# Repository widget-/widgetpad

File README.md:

# Widgetpad v0

Hi, I'm Widget, and these are the files for my ITG dance/travel pad.

This is the "v0" version, currently in prototype status. I don't plan
on deviating too far from these plans, but there are more adjustments
I still want to make to make the pad easier to manufacture, easier to
fork the source code for, and have it perform more consistently.

You can find me on the Stamina Nation discord causing problems in #pads.

If you live in Chicago and can pass stamina 16's or higher, I would be
interested in having you try out the prototype in person for feedback.
Let me know on Discord.

## Motivation

Current pads either suck or are >$1000. LTEKs are acceptable but need
significant modding using custom microcontrollers and the fragile "penny
mod", so why not just make a new pad?

Currently it's mainly competing with Bandit's
[Build This Travel Pad](https://www.youtube.com/watch?v=y6wGYLE0YI4)
and [Bandit's Terrific Travel Pad](https://github.com/BanditsTerrificTravelPad/bttp)
budget designs.

## Specs

* Aluminum extrusion frame (2020 profile)
* 1/2" acrylic panels
* Arduino Pro Micro microcontroller (but with plans to switch to Teensy
  4.0)
* Force-sensitive resistors for configurable sensitivity
  * Allows for rather extreme sensitivity if made with good tolerances
* Optional LED grid PCBs (WS2812C LEDs)

## License

GNU GPL v2. See LICENSE for full text.

## Demo

## Requirements

### Materials

* Arduino Pro Micro or Teensy 2.0 or higher
* 4x 220 ohm resistors
* Some wire to extend FSR connections
* Panels, cut or precut:
  * Either
    * 4x 12mm thickness 280mm x 280mm acrylic panels (1/2" thickness
      11"x11") or larger
  * Or
    * 1x 280mm x 280mm precut acrylic center panel
    * 4x 280mm x 125mm precut acrylic side panels
    * 4x 125mm x 125mm precut acrylic corner panels (optional)
  * Optionally, acetal (a.k.a. POM, Delrin) as a slipperier center panel
    instead of acrylic
* Aluminum extrusion (2020 profile)
  * All taps should be M6 taps with 10mm depth
    * Extra depth is acceptable but may require longer M6 threaded rods
  * 2x 544mm extrusions
    * Drill 6mm at holes at 10mm, 129.5mm, 414.5mm, and 534mm
    * Countersink these holes for your 6mm bolts as well
  * 4x 504mm extrusions, both ends tapped
    * Drill 6mm holes at 109.5mm and 394.5mm
    * For 2 extrusions, countersink these holes for your 6mm bolts as
      well
    * For the other 2 extrusions, extra holes for wiring recommended
  * 2x 265mm extrusions, both ends tapped
    * Extra holes through the center for wiring recommended
  * 4x 99.5mm extrusions, both ends tapped
    * Extra holes through the center for wiring recommended
* Force sensitive resistors (4x 200mm [Interlink 408](https://buyinterlinkelectronics.com/collections/new-standard-force-sensors/products/fsr-model-408-200mm-length) or 8x
  [Interlink 400](https://buyinterlinkelectronics.com/collections/new-standard-force-sensors/products/fsr-model-400))
* 12x countersunk M6x30mm bolts
* 12x hex-head M6x30mm bolts
* 4x M6x40mm threaded rods
* 16x M6 threaded inserts for plastic
* 40x M5x10 bolts
* 40x M5 hammer nuts for 2020 aluminum extrusion
* An "engineering" filament for 3D printed parts, such as PETG, nylon,
  or polycarbonate
* Optional: cross brackets and angle brackets for stability
* Optional: rubber bumpers for floor safety and/or better pad sensitivity
* Optional: 128 [WS2812C-5050](https://lcsc.com/product-detail/Light-Emitting-Diodes-LED_5050-RGBIntegrated-Light-4Pin_C114587.html) LEDs for PCBs
* Optional: 8x 1x2 2.54mm-pitch right-angle male PCB headers for PCBs
* Optional: 4x [5.04mm-pitch 1x2 screw terminals](https://lcsc.com/product-detail/Screw-terminal_Ningbo-Kangnex-Elec-WJ500V-5-08-2P_C8465.html) for PCBs
* Optional: 8x [5.04mm-pitch 1x3 screw terminals](https://lcsc.com/product-detail/Screw-terminal_Ningbo-Kangnex-Elec-WJ500V-5-08-3P_C72334.html) for PCBs

### Equipment

* Table saw if acrylic cutting needed
* Drill press with 6mm (1/4") drill bit and 45° countersink bit
* Table router and roundover bit or lots of sandpaper for smooth edges
* 3mm and 4mm allen keys
* 3D printer for panel mounts
* A heated tool of some sort, such as a soldering iron or a lighter and
  a rod of some type, for inserting the threaded inserts
* Soldering iron is required if assembling PCBs
* DuPont wire crimpers may be useful for making "extension cords" for
  the FSR connectors

### 3D printed parts

3D printed parts can be found in the `3d/` folder.

Parts are designed using [OpenSCAD](https://openscad.org/) with the
[BOSL2](https://github.com/revarbat/BOSL2) library. OpenSCAD nightlies
and BOSL2 master branch are recommended.

Corner bracket mounts will need to be 3D printed to connect the panels
to the aluminum frame.

Strong filaments, at a minimum PETG but preferably
nylon or polycarbonate will be required. Brittle filaments like PLA,
ABS, HIPS, and ASA may crack. High-rigidity TPU filaments (Shore
hardness 98A or higher) may work, but soft filaments may cause the
panels to slide during play.

A soldering iron or other heating tool will be needed to melt the
threaded inserts into the 3D printed part for the panels to connect to.

PCB mounts may also be 3D printed.

A housing will eventually be designed for the microcontroller but not
as part of v0.

### PCBs

#### Microcontroller breakout

The microcontroller breakout is for a Teensy 4.0 or Teensy 4.1.

The Teensy 4.0 will allow control of up to 10 FSRs, which can map to
up to 10 panels, or 2 FSRs on up to 5 panels.

The Teensy 4.1 will allow control of up to 18 FSRs, which allows an
amount of flexibility with regards to a high-end setup:

* 4 FSRs on each of 4 panels (dance)
* 2 FSRs on each of 8 or 9 panels (techno)
* 2 or 3 FSRs on 4 panels and 4 on a center panel (pump)
* 4 FSRs on 4 panels, and 2 on a center panel (pump)

The breakout also has:

* A 3-pin JST-HX connection for panel LEDs
* 9 LEDs for checking FSR pressed status
* 4 external buttons, for an external arcade button assembly
* 3 internal buttons for controlling LED brightness, and triggering
  an as-yet-unwritten pad calibration
* A buzzer or speaker, to add audio "tactility" to pressing the panels
* A jumper to bridge USB power with the external power input for LEDs

The breakout is designed using KiCAD and uses
[teensy_library](https://github.com/XenGi/teensy_library) and
[teensy.pretty](https://github.com/XenGi/teensy.pretty) by
[XenGi](https://github.com/XenGi), released under the BSD license.

#### Panels

The PCBs are designed using [KiCAD](https://www.kicad.org/).

The PCBs each hold an 8x4 grid of WS2812C LEDs. An external 5V power
source is recommended if using LEDs.

Each PCB has screw terminals for connecting the WS2812C inputs and
outputs. In addition, there are 3 positions of screw terminals and
headers for connecting one or more FSRs. Multiple FSRs would be wired
in parallel.

## Construction

### Frame

1) Cut all aluminum extrusion pieces to length, if not precut
2) Cut drills and countersinks in extrusion
3) Tap all extrusion pieces 10mm deep except the two longest ones, if
   not pretapped
4) Use threaded rods to attach small extrusions "through" the two longer
   center ones
5) Bolt the four second-longest extrusions to the longest two extrusions
6) Insert threaded inserts (using heat) into 3D printed panel mounts
7) Attach 3D printed panel mounts to corners of frame using M5 hammer
   nuts
8) Optionally add cross braces and corner brackets, and add rubber feet
   to the bottom of the frame

### Panels

1) Cut all panels to correct size
2) Preferably using a drill press, cut holes 30mm inset from each corner
   * Four holes on the center panel
   * Two adjacent holes on the edge panels
   * Two opposing holes on the corner panels
3) Use a countersink bit to countersink the holes
4) Using a table router with a roundover bit or lots of sandpaper,
   smooth the edges so that your socks don't get torn up

### Wiring

This pad uses typical wiring for FSR-based pads. Each FSR should connect
to an analog pin an the microcontroller with a 220 ohm pulldown resistor
with the other side connected to VCC.

LED boards will need a connection to VCC, GND, and a data pin, typically
D10 on the Arduino Pro Micro.

An external 5V power source is recommended if using LEDs.

One or more large capacitors (47μF or larger) across +5V and GND may
help with signal stability if the LEDs are causing noise in the FSR
signals.

See also [this diagram](https://cdn.discordapp.com/attachments/591851159795400734/841802090543054849/Untitled-1.png) by Bandit.

## Dimensions

The dimensions are currently calculated using Fusion 360, but I hate
Fusion 360 so eventually I'll change it over to OpenSCAD as well.

## Firmware

The firmware is still a work in progress and can be found at
[widget-/bttp-firmware](https://github.com/widget-/bttp-firmware). It is
a fork of Bandit's [BTTP](https://github.com/BanditsTerrificTravelPad/bttp)
pad's firmware.

Currently it supports joystick or keyboard input, and allows an arbitrary
amount of buttons with corresponding optional LED strips. Sensitivity
can be adjusted either in the firmware or with a tool such as the
[bttp-config-tool](https://github.com/BanditsTerrificTravelPad/bttp-config-tool).

## Special thanks

* Bandit, for motivating me to make this pad, as well as giving me one
  of his prototype pads to play on.
* [dominick](https://www.youtube.com/channel/UCpeNRVOVrqx_lras7hbOOrQ)
  and [teejusb](https://github.com/teejusb) for their help and experience
* The rest of #pads for keeping me motivated
* [South Side Hackerspace](https://sshchicago.org/), for having all the equipment used to create
  the prototype

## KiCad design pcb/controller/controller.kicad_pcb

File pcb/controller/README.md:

# Teensy 4.0/4.1 Breakout PCB

This is a breakout board for the Teensy 4.0 or Teensy 4.1
microcontroller, intended for use with custom dance pads for games like
ITG and Pump It Up.

This PCB is designed in KiCAD. If the dependencies for the board are not
detected automatically, add the common_lib folder next to this folder
to your KiCAD's search paths for both libraries and footprints.

## Features

* Many FSR outputs with 10kΩ resistors
  * 18 outputs with Teensy 4.1
  * 10 outputs with Teensy 4.0
* Status LEDs for FSR activation status
* 3-pin JST-XH connector for WS2811/WS2812 panel LED boards or strips
* Internal buttons for controlling LED brightness and activating pad
  automatic calibration
* Connection points for external navigation buttons
* Buzzer for audio feedback
* DC barrel jack connector for external LED power
  * Jumper for using USB power to power LEDs instead
* Headers for all soldered Teensy pins, to allow for use cases beyond
  just this board

## License

GNU GPL v2. See the LICENSE file in this project's root for full text.

## Schematic

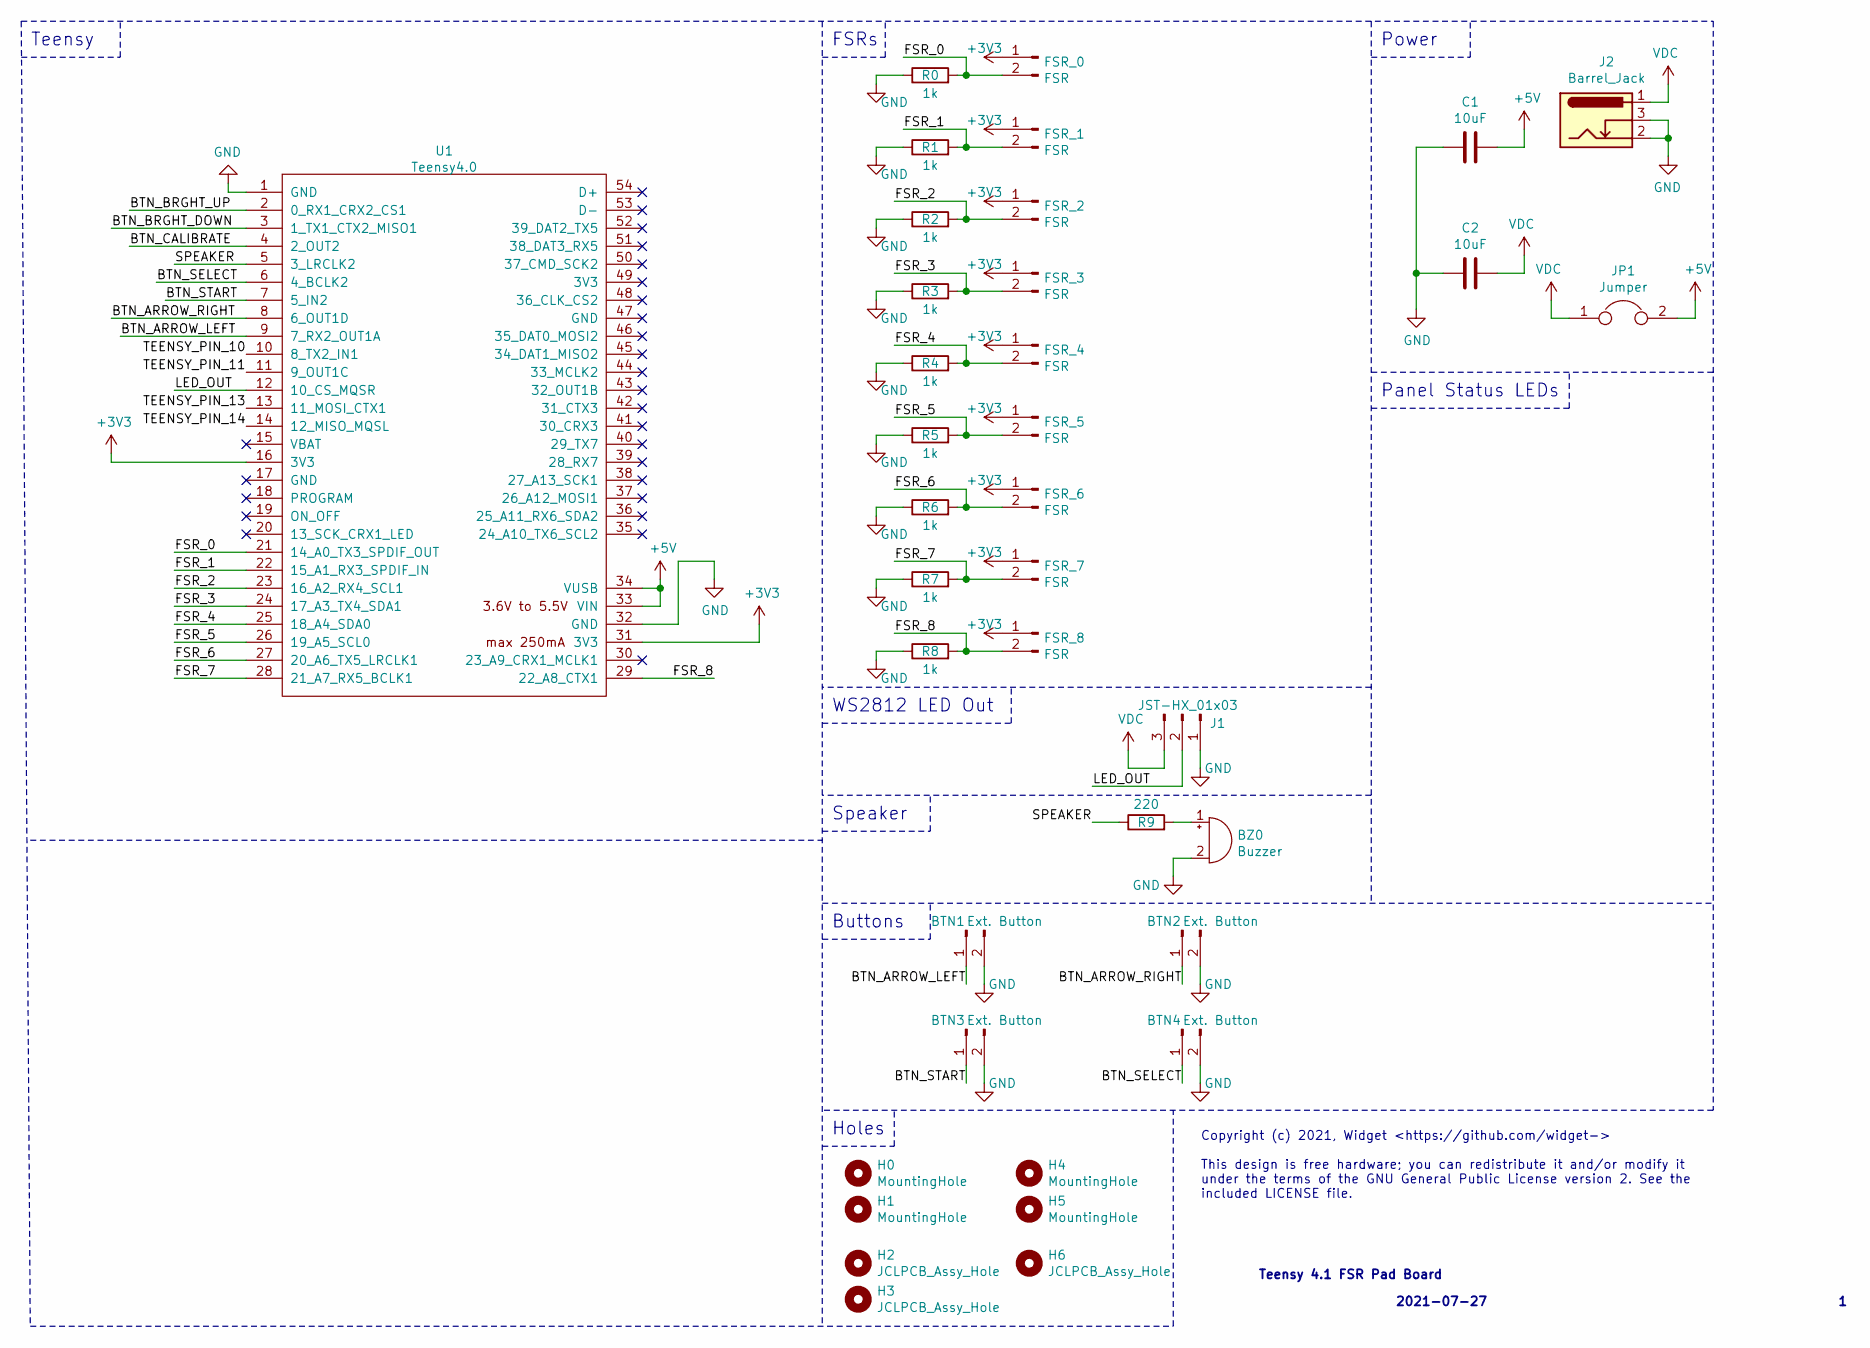
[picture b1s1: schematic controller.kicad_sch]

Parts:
BTN1, BTN2, BTN3, BTN4: Ext. Button; PinHeader_1x02_P2.54mm_Horizontal
BZ0: Buzzer; Buzzer_12x9.5RM7.6
C1, C2: 10uF; C_0805_2012Metric
FSR_0, FSR_1, FSR_2, FSR_3, FSR_4, FSR_5, FSR_6, FSR_7, FSR_8: FSR; PinHeader_1x02_P2.54mm_Horizontal
H0, H1, H4, H5: MountingHole; MountingHole_3.2mm_M3
H2, H3, H6: JCLPCB_Assy_Hole; JCLPCB_Assembly_Hole
J1: JST-HX_01x03; JST_XH_B3B-XH-AM_1x03_P2.50mm_Vertical
J2: Barrel_Jack; XKB_Connectivity_DC-044A-2.5A
JP1: Jumper; PinHeader_1x02_P2.54mm_Vertical
R0, R1, R2, R3, R4, R5, R6, R7, R8: 1k; R_0805_2012Metric_Pad1.20x1.40mm_HandSolder
R9: 220; R_0805_2012Metric_Pad1.20x1.40mm_HandSolder
U1: Teensy4.0; teensy40

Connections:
+3V3: FSR_0.1, FSR_1.1, FSR_2.1, FSR_3.1, FSR_4.1, FSR_5.1, FSR_6.1, FSR_7.1, FSR_8.1, U1.16 (3V3), U1.31 (3V3)
+5V: C1.1, JP1.2, U1.33 (VIN), U1.34 (VUSB)
/BTN_ARROW_LEFT: BTN1.1, U1.9 (7_RX2_OUT1A)
/BTN_ARROW_RIGHT: BTN2.1, U1.8 (6_OUT1D)
/BTN_BRGHT_DOWN: U1.3 (1_TX1_CTX2_MISO1)
/BTN_BRGHT_UP: U1.2 (0_RX1_CRX2_CS1)
/BTN_CALIBRATE: U1.4 (2_OUT2)
/BTN_SELECT: BTN4.1, U1.6 (4_BCLK2)
/BTN_START: BTN3.1, U1.7 (5_IN2)
/FSR_0: FSR_0.2, R0.2, U1.21 (14_A0_TX3_SPDIF_OUT)
/FSR_1: FSR_1.2, R1.2, U1.22 (15_A1_RX3_SPDIF_IN)
/FSR_2: FSR_2.2, R2.2, U1.23 (16_A2_RX4_SCL1)
/FSR_3: FSR_3.2, R3.2, U1.24 (17_A3_TX4_SDA1)
/FSR_4: FSR_4.2, R4.2, U1.25 (18_A4_SDA0)
/FSR_5: FSR_5.2, R5.2, U1.26 (19_A5_SCL0)
/FSR_6: FSR_6.2, R6.2, U1.27 (20_A6_TX5_LRCLK1)
/FSR_7: FSR_7.2, R7.2, U1.28 (21_A7_RX5_BCLK1)
/FSR_8: FSR_8.2, R8.2, U1.29 (22_A8_CTX1)
/LED_OUT: J1.2, U1.12 (10_CS_MQSR)
/SPEAKER: R9.1, U1.5 (3_LRCLK2)
/TEENSY_PIN_10: U1.10 (8_TX2_IN1)
/TEENSY_PIN_11: U1.11 (9_OUT1C)
/TEENSY_PIN_13: U1.13 (11_MOSI_CTX1)
/TEENSY_PIN_14: U1.14 (12_MISO_MQSL)
GND: BTN1.2, BTN2.2, BTN3.2, BTN4.2, BZ0.2 (+), C1.2, C2.2, J1.1, J2.2, J2.3, R0.1, R1.1, R2.1, R3.1, R4.1, R5.1, R6.1, R7.1, R8.1, U1.1 (GND), U1.32 (GND)
unnamed: BZ0.1 (-), R9.2
VDC: C2.1, J1.3, J2.1, JP1.1

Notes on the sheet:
Teensy
FSRs
WS2812 LED Out
Speaker
Buttons
Holes
Copyright (c) 2021, Widget <https://github.com/widget-> This design is free hardware; you can redistribute it and/or modify it under the terms of the GNU General Public License version 2. See the included LICENSE file.
Power
Panel Status LEDs
Teensy 4.1 FSR Pad Board
2021-07-27

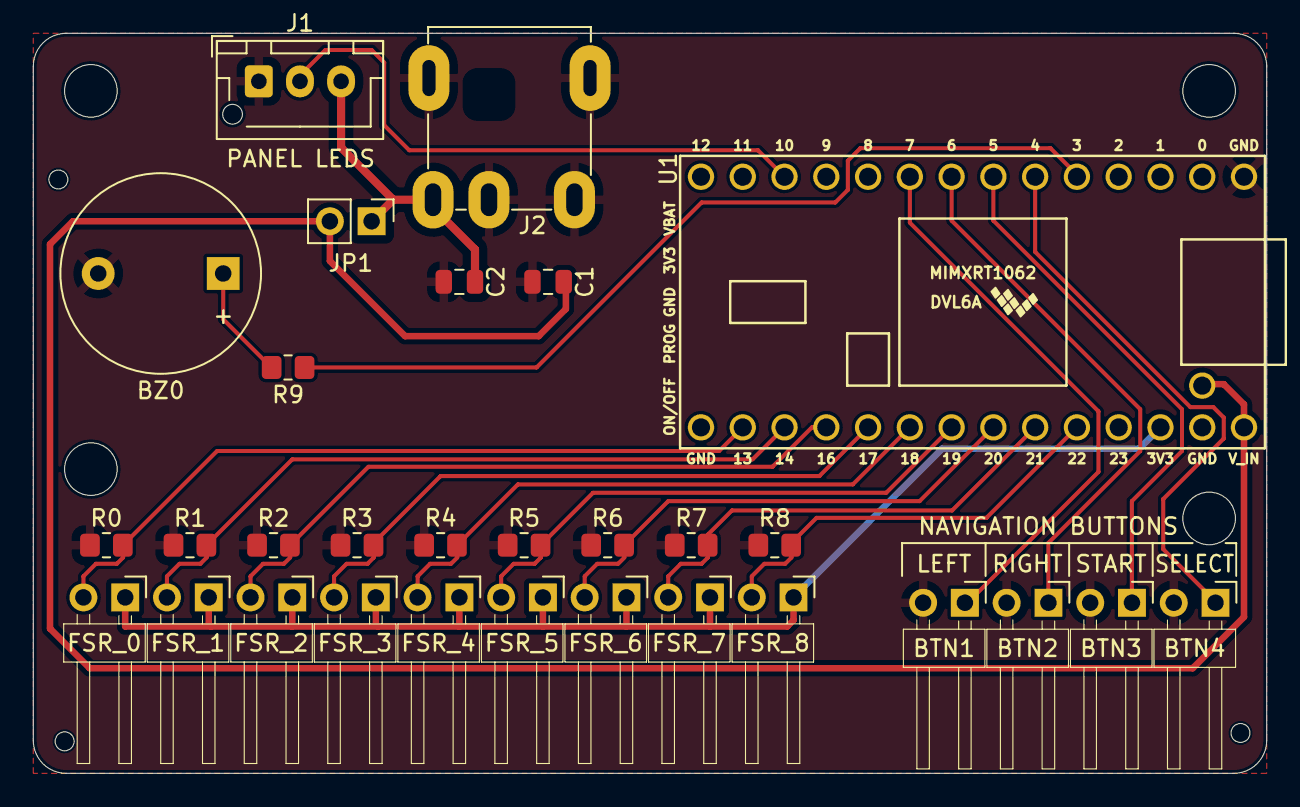
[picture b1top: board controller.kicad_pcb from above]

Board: 2 copper layers, 75.0 x 45.0 mm, 37 parts (0 on the bottom side), 20 nets.

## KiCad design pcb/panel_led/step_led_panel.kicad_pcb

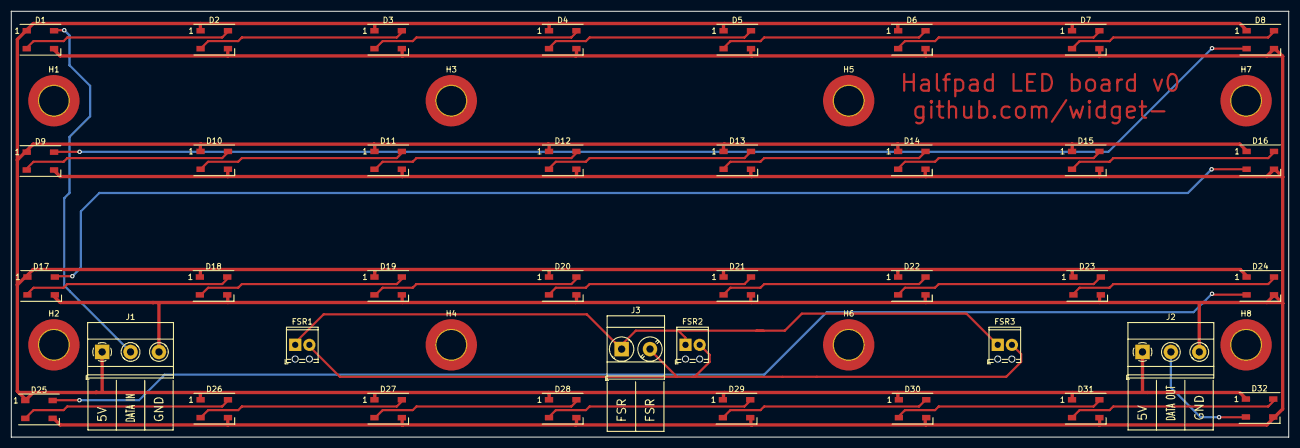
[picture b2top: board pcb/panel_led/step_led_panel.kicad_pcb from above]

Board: 2 copper layers, 228.6 x 76.2 mm, 46 parts (0 on the bottom side), 37 nets.

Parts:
D1, D2, D3, D4, D5, D6, D7, D8, D9, D10, D11, D12, D13, D14, D15, D16, D17, D18, D19, D20, D21, D22, D23, D24, D25, D26, D27, D28, D29, D30, D31, D32: WS2812; LED_WS2812B_PLCC4_5.0x5.0mm_P3.2mm
FSR1, FSR2, FSR3: Screw_Terminal_01x02; TerminalBlock_Phoenix_MPT-0,5-2-2.54_1x02_P2.54mm_Horizontal
H1, H2, H3, H4, H5, H6, H7, H8: MountingHole; MountingHole_5.3mm_M5_DIN965_Pad_TopOnly
J1, J2: Screw_Terminal_01x03; TerminalBlock_Phoenix_MKDS-1,5-3-5.08_1x03_P5.08mm_Horizont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
J3: Screw_Terminal_01x02; TerminalBlock_Phoenix_MKDS-3-2-5.08_1x02_P5.08mm_Horizontal

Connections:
+5V: D1.1, D2.1, D3.1, D4.1, D5.1, D6.1, D7.1, D8.1, D10.1, D11.1, D12.1, D13.1, D14.1, D15.1, D16.1, D18.1, D19.1, D20.1, D21.1, D22.1, D23.1, D24.1, D26.1, D27.1, D28.1, D29.1, D30.1, D31.1, D32.1, J1.1, J2.1
/D_IN: D1.4, J1.2
/D_OUT: D32.2, J2.2
GND: D1.3, D2.3, D3.3, D4.3, D5.3, D6.3, D7.3, D8.3, D10.3, D11.3, D12.3, D13.3, D14.3, D15.3, D16.3, D18.3, D19.3, D20.3, D21.3, D22.3, D23.3, D24.3, D26.3, D27.3, D28.3, D29.3, D30.3, D31.3, D32.3, J1.3, J2.3
unnamed: D1.2, D2.4
unnamed: D2.2, D3.4
unnamed: D3.2, D4.4
unnamed: D4.2, D5.4
unnamed: D5.2, D6.4
unnamed: D6.2, D7.4
unnamed: D7.2, D8.4
unnamed: D8.2, D9.4
unnamed: D10.2, D11.4
unnamed: D9.2, D10.4
unnamed: D11.2, D12.4
unnamed: D12.2, D13.4
unnamed: D13.2, D14.4
unnamed: D14.2, D15.4
unnamed: D15.2, D16.4
unnamed: D16.2, D17.4
unnamed: D17.2, D18.4
unnamed: D18.2, D19.4
unnamed: D19.2, D20.4
unnamed: D20.2, D21.4
unnamed: D21.2, D22.4
unnamed: D22.2, D23.4
unnamed: D23.2, D24.4
unnamed: D24.2, D25.4
unnamed: D25.2, D26.4
unnamed: D26.2, D27.4
unnamed: D27.2, D28.4
unnamed: D28.2, D29.4
unnamed: D29.2, D30.4
unnamed: D30.2, D31.4
unnamed: D31.2, D32.4
unnamed: FSR1.1, FSR2.1, FSR3.1, J3.1
unnamed: FSR1.2, FSR2.2, FSR3.2, J3.2

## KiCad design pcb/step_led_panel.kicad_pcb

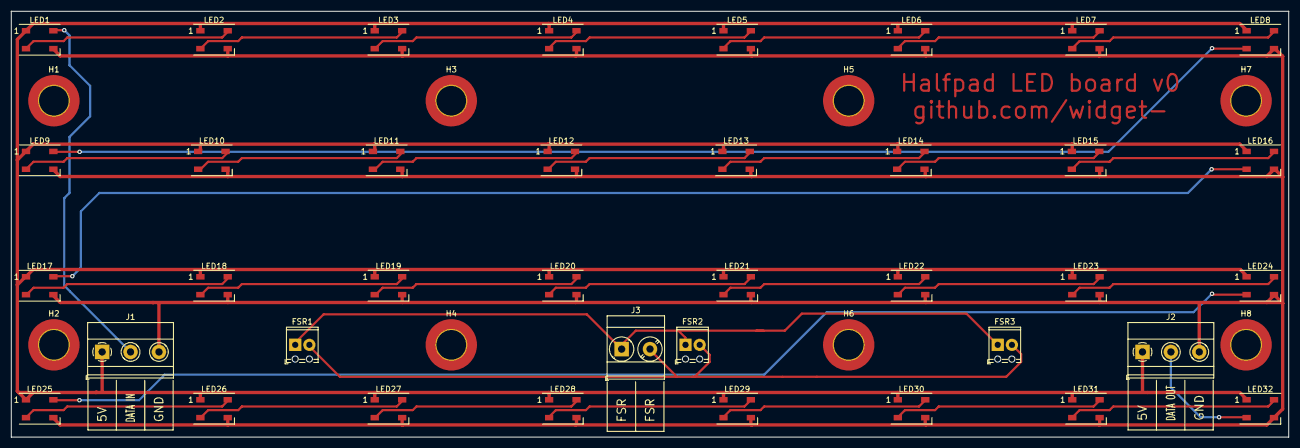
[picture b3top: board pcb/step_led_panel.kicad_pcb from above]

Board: 2 copper layers, 228.6 x 76.2 mm, 46 parts (0 on the bottom side), 37 nets.

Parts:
FSR1, FSR2, FSR3: Screw_Terminal_01x02; TerminalBlock_Phoenix_MPT-0,5-2-2.54_1x02_P2.54mm_Horizontal
H1, H2, H3, H4, H5, H6, H7, H8: MountingHole; MountingHole_5.3mm_M5_DIN965_Pad_TopOnly
J1, J2: Screw_Terminal_01x03; TerminalBlock_Phoenix_MKDS-1,5-3-5.08_1x03_P5.08mm_Horizont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
J3: Screw_Terminal_01x02; TerminalBlock_Phoenix_MKDS-3-2-5.08_1x02_P5.08mm_Horizontal
LED1, LED2, LED3, LED4, LED5, LED6, LED7, LED8, LED9, LED10, LED11, LED12, LED13, LED14, LED15, LED16, LED17, LED18, LED19, LED20, LED21, LED22, LED23, LED24, LED25, LED26, LED27, LED28, LED29, LED30, LED31, LED32: WS2812B; LED_WS2812B_PLCC4_5.0x5.0mm_P3.2mm

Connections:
+5V: J1.1, J2.1, LED1.1, LED2.1, LED3.1, LED4.1, LED5.1, LED6.1, LED7.1, LED8.1, LED9.1, LED10.1, LED11.1, LED12.1, LED13.1, LED14.1, LED15.1, LED16.1, LED17.1, LED18.1, LED19.1, LED20.1, LED21.1, LED22.1, LED23.1, LED24.1, LED25.1, LED26.1, LED27.1, LED28.1, LED29.1, LED30.1, LED31.1, LED32.1
/D_IN: J1.2, LED1.4
/D_OUT: J2.2, LED32.2
GND: J1.3, J2.3, LED1.3, LED2.3, LED3.3, LED4.3, LED5.3, LED6.3, LED7.3, LED8.3, LED9.3, LED10.3, LED11.3, LED12.3, LED13.3, LED14.3, LED15.3, LED16.3, LED17.3, LED18.3, LED19.3, LED20.3, LED21.3, LED22.3, LED23.3, LED24.3, LED25.3, LED26.3, LED27.3, LED28.3, LED29.3, LED30.3, LED31.3, LED32.3
unnamed: FSR1.1, FSR2.1, FSR3.1, J3.1
unnamed: FSR1.2, FSR2.2, FSR3.2, J3.2
unnamed: LED1.2, LED2.4
unnamed: LED2.2, LED3.4
unnamed: LED3.2, LED4.4
unnamed: LED4.2, LED5.4
unnamed: LED5.2, LED6.4
unnamed: LED6.2, LED7.4
unnamed: LED7.2, LED8.4
unnamed: LED8.2, LED9.4
unnamed: LED10.2, LED11.4
unnamed: LED9.2, LED10.4
unnamed: LED11.2, LED12.4
unnamed: LED12.2, LED13.4
unnamed: LED13.2, LED14.4
unnamed: LED14.2, LED15.4
unnamed: LED15.2, LED16.4
unnamed: LED16.2, LED17.4
unnamed: LED17.2, LED18.4
unnamed: LED18.2, LED19.4
unnamed: LED19.2, LED20.4
unnamed: LED20.2, LED21.4
unnamed: LED21.2, LED22.4
unnamed: LED22.2, LED23.4
unnamed: LED23.2, LED24.4
unnamed: LED24.2, LED25.4
unnamed: LED25.2, LED26.4
unnamed: LED26.2, LED27.4
unnamed: LED27.2, LED28.4
unnamed: LED28.2, LED29.4
unnamed: LED29.2, LED30.4
unnamed: LED30.2, LED31.4
unnamed: LED31.2, LED32.4

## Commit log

2021-07-08 Initial revision for v0 of pad
2021-07-08 Update README.md with more information
2021-07-08 Fix edge panel dimensions
2021-07-20 Move panel PCB to its own subfolder
2021-07-26 Add controller PCB schematic and unrouted layout
2021-07-26 Update README.md for microcontroller breakout
2021-07-26 Controller Breakout board v0
2021-07-26 Rename pcb/panel to pcb/panel_led
2021-08-04 Finalize v0.1 of breakout board to start v0.2
2021-12-15 Schematic and layout of v0.2
2021-12-15 Widgetpad controller v0.2

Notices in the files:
pcb/controller/controller.kicad_pcb:
©Widget 2022, Licensed GPLv2
